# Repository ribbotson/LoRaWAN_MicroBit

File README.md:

# LoRaWAN_MicroBit
This is a free open source LoRaWAN interface for BBC Microbit including power control timer

## Content

This is a hardware project with PCB design file in Eagle. 

## Authors

* **Richard Ibbotson**  

## License

Hardware is Licensed under CERN OHL v.1.2 or later https://www.ohwr.org/documents/294 No warranty is provided for this documentation implied or otherwise.

Software is licensed under MIT License.

MIT License

Copyright (c) 2017 Richard Ibbotson
richard.ibbotson@ribbotson.com

Permission is hereby granted, free of charge, to any person obtaining a copy
of this software and associated documentation files (the "Software"), to deal
in the Software without restriction, including without limitation the rights
to use, copy, modify, merge, publish, distribute, sublicense, and/or sell
copies of the Software, and to permit persons to whom the Software is
furnished to do so, subject to the following conditions:

The above copyright notice and this permission notice shall be included in all
copies or substantial portions of the Software.

THE SOFTWARE IS PROVIDED "AS IS", WITHOUT WARRANTY OF ANY KIND, EXPRESS OR
IMPLIED, INCLUDING BUT NOT LIMITED TO THE WARRANTIES OF MERCHANTABILITY,
FITNESS FOR A PARTICULAR PURPOSE AND NONINFRINGEMENT. IN NO EVENT SHALL THE
AUTHORS OR COPYRIGHT HOLDERS BE LIABLE FOR ANY CLAIM, DAMAGES OR OTHER
LIABILITY, WHETHER IN AN ACTION OF CONTRACT, TORT OR OTHERWISE, ARISING FROM,
OUT OF OR IN CONNECTION WITH THE SOFTWARE OR THE USE OR OTHER DEALINGS IN THE
SOFTWARE.

## Acknowledgments

* All the folks at [rLab](http://www.rlab.org.uk) Reading Hackspace especially mikethebee
+ [Hackaday.io](https://hackaday.io/project/12164-just-do-iot) for featuring the project
+ [The Things Network](https://www.thethingsnetwork.org/)

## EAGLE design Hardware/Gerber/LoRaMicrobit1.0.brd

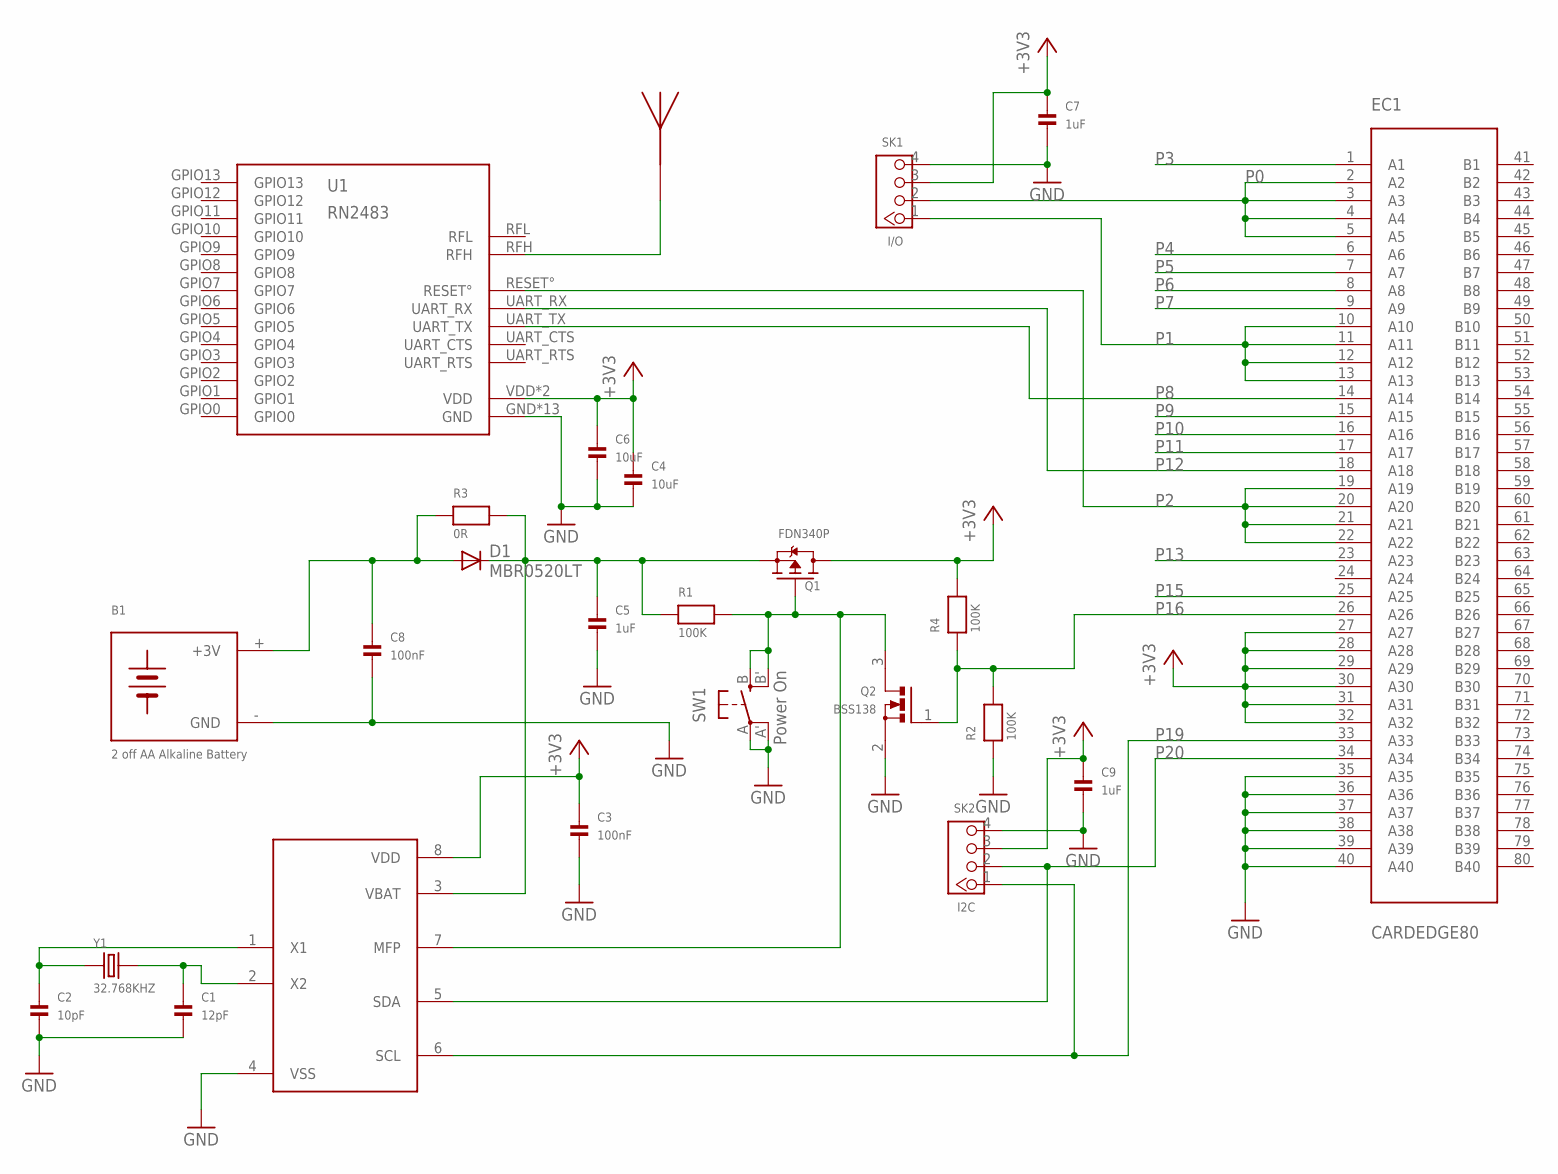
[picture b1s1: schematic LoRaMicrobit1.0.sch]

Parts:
B1: 2 off AA Alkaline Battery; 2AABATTERY
C1: 12pF; 0603
C2: 10pF; 0603
C3, C8: 100nF; 0603
C4, C6: 10uF; 0603
C5, C7, C9: 1uF; 0603
D1: MBR0520LT; SOD123
EC1: CARDEDGE80
Q1: FDN340P; SOT23-R
Q2: BSS138; SOT23-R
R1, R2, R4: 100K; 0603
R3: 0R; 0603
SK1: I/O; HW4-2.0-90D
SK2: I2C; HW4-2.0-90D
SW1: Power On; EVQ-Q2
U1: RN2483
U2: MCP7940N; SOIC8-N_MC
U$2: 0868AT43A0020; 0868AT043A0020
Y1: 32.768KHZ; X2-SMD-3.2X1.5X0.55MM

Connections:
+3V3: C3.1, C4.1, C6.1, C7.1, C9.1, EC1.27 (A27), EC1.28 (A28), EC1.29 (A29), EC1.30 (A30), EC1.31 (A31), EC1.32 (A32), Q1.3 (D), R4.2, SK1.3, SK2.3, U1.VDD, U1.VDD2 (VDD), U2.8 (VDD)
GND: B1.- (GND), C1.2, C2.2, C3.2, C4.2, C5.2, C6.2, C7.2, C8.2, C9.2, EC1.35 (A35), EC1.36 (A36), EC1.37 (A37), EC1.38 (A38), EC1.39 (A39), EC1.40 (A40), Q2.2 (S), R2.1, SK1.4, SK2.4, SW1.A, SW1.A' (P1), U1.GND, U1.GND1 (GND), U1.GND2 (GND), U1.GND3 (GND), U1.GND4 (GND), U1.GND5 (GND), U1.GND6 (GND), U1.GND7 (GND), U1.GND8 (GND), U1.GND9 (GND), U1.GND10 (GND), U1.GND11 (GND), U1.GND12 (GND), U2.4 (VSS)
unnamed: U1.RFH, U$2.P$1
unnamed: C2.1, U2.1 (X1), Y1.1
unnamed: C1.1, U2.2 (X2), Y1.2
unnamed: B1.+ (+3V), C8.1, D1.A, R3.1
unnamed: C5.1, D1.C, Q1.2 (S), R1.1, R3.2, U2.3 (VBAT)
unnamed: Q1.1 (G), Q2.3 (D), R1.2, SW1.B (S), SW1.B' (S1), U2.7 (MFP)
P0: EC1.2 (A2), EC1.3 (A3), EC1.4 (A4), EC1.5 (A5), SK1.2
P1: EC1.10 (A10), EC1.11 (A11), EC1.12 (A12), EC1.13 (A13), SK1.1
P2: EC1.19 (A19), EC1.20 (A20), EC1.21 (A21), EC1.22 (A22), U1.RESET°
P3: EC1.1 (A1)
P4: EC1.6 (A6)
P5: EC1.7 (A7)
P6: EC1.8 (A8)
P7: EC1.9 (A9)
P8: EC1.14 (A14), U1.UART_TX
P9: EC1.15 (A15)
P10: EC1.16 (A16)
P11: EC1.17 (A17)
P12: EC1.18 (A18), U1.UART_RX
P13: EC1.23 (A23)
P15: EC1.25 (A25)
P16: EC1.26 (A26), Q2.1 (G), R2.2, R4.1
P19: EC1.33 (A33), SK2.1, U2.6 (SCL)
P20: EC1.34 (A34), SK2.2, U2.5 (SDA)

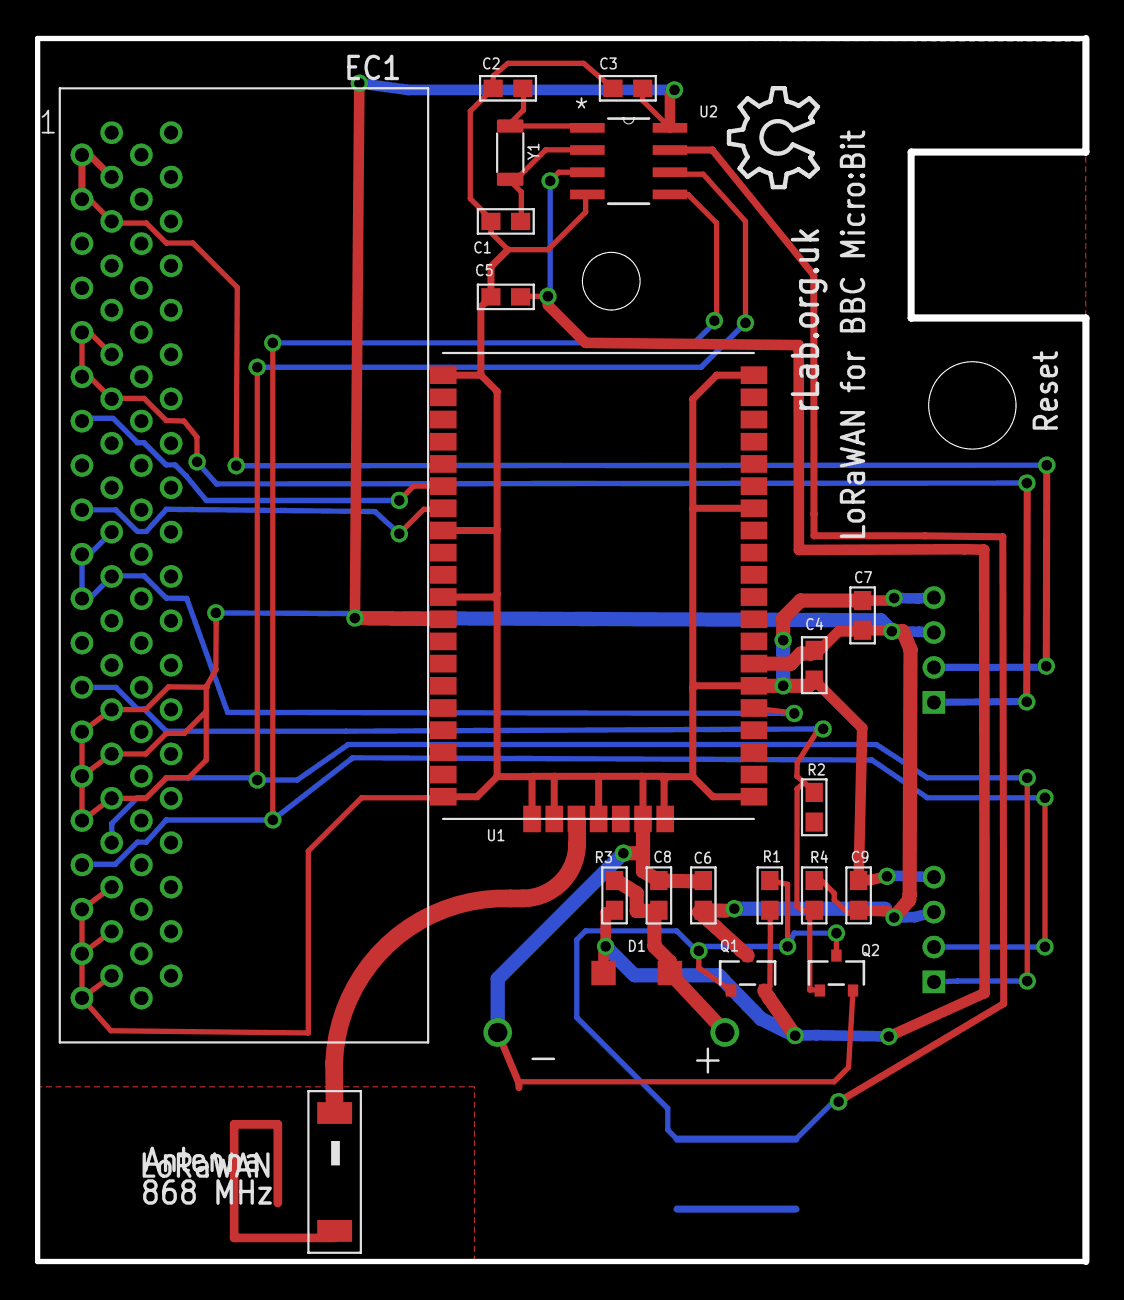
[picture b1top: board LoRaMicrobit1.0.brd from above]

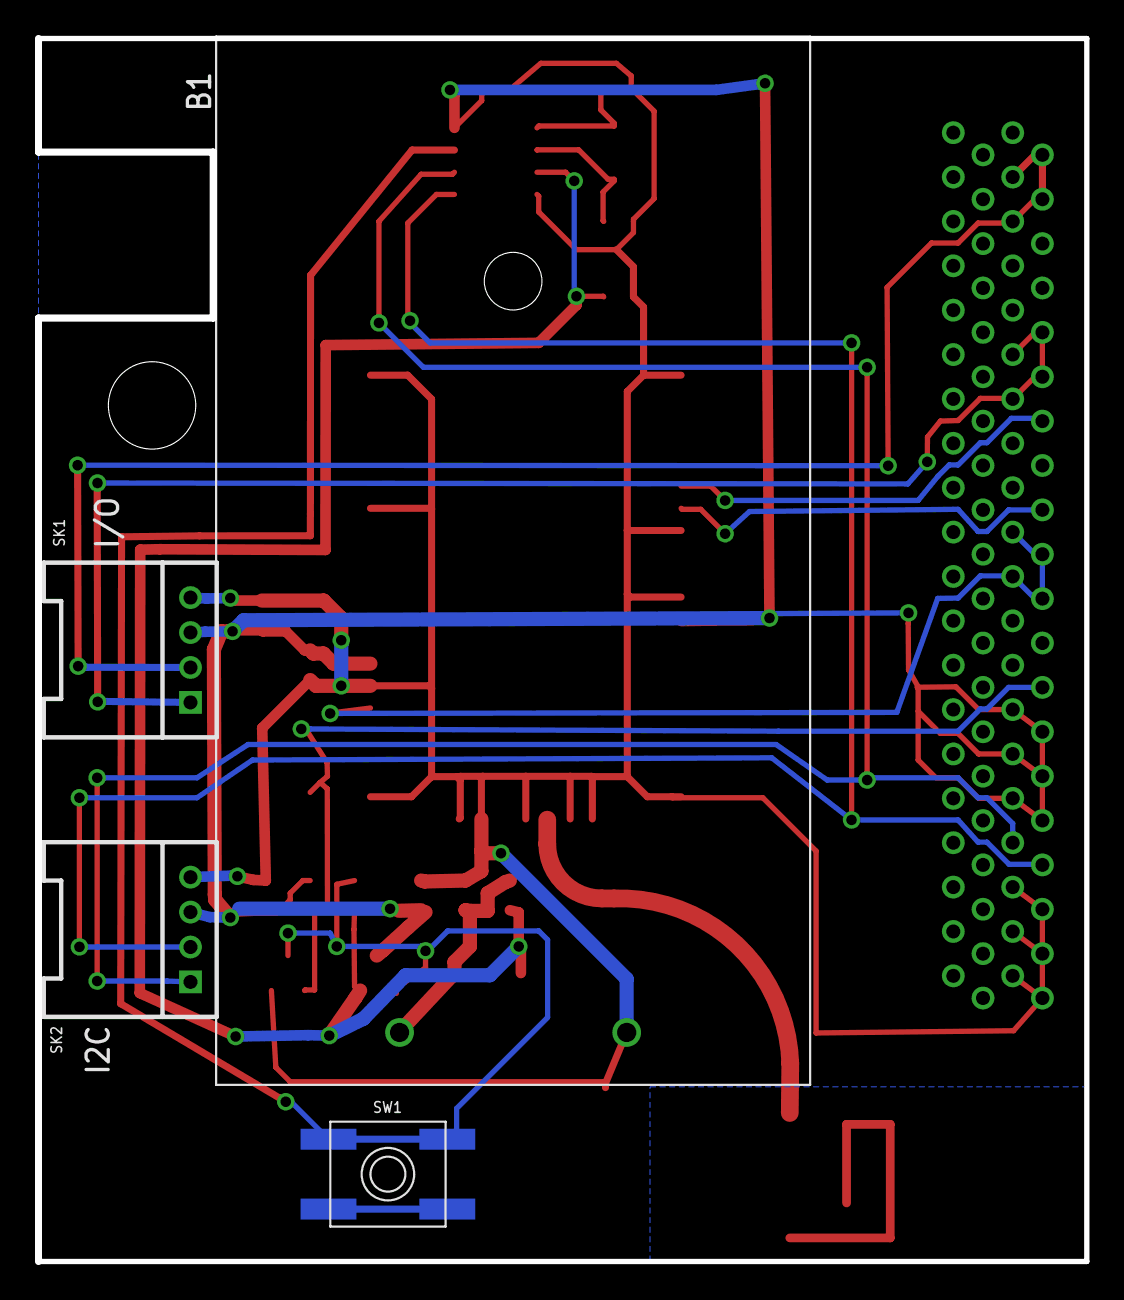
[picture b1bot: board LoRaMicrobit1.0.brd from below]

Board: 2 copper layers, 59.9 x 70.0 mm, 26 parts (4 on the bottom side), 16 nets.

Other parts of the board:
U$1: OSHW_10X200_NOTEXT

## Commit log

2016-07-22 :space_invader: Added .gitattributes & .gitignore files
2016-07-22 LoRaWAN for Micro:Bit
2016-07-30 MicroBit MicroPython files
2017-09-07 Minor layout change to avoid reset witch

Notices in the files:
parts and their libraries:
microbuilder: This work is placed in the public domain, and may be freely used for commercial and non-commercial work with the following conditions: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
